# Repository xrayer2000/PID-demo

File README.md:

# PID-DEMO

A dual-axis stepper motor control system based on an STM32F411 microcontroller. The project implements closed-loop position and velocity control using magnetic rotary encoders, PID controllers and configurable motion profiles.

## Mechanical Assembly

The project incorporates three cycloidal reducer designs:

- **Left:** Cycloidal reducers driven by stepper motors, designed by [SweepDynamics](https://github.com/SweepDynamics) and [Promakina](https://github.com/Promakina), respectively.
- **Right:** Cycloidal reducer driven by a BLDC motor, designed by [sirojudinMunir](https://github.com/sirojudinMunir) ([SF-Motion](https://github.com/sirojudinMunir/sf-motion)).

## Features

- **Dual-axis control** – independent control of two stepper motor axes.
- **Closed-loop feedback** – AS5600 magnetic rotary encoders provide position feedback.
- **PID control** – separate position and velocity PID controllers for each axis.
- **Motion profiling** – trapezoidal and triangular position profiles, as well as velocity ramps.
- **Multiple operating modes** – position control, position oscillation, velocity control and velocity oscillation.
- **Configurable parameters** – setpoints, PID gains, oscillation amplitude, period, motor microstepping and step signal duty cycle.
- **OLED interface** – two displays and a rotary encoder with push-button navigation.
- **FreeRTOS** – separate tasks for control, display and main application logic.
- **Serial monitoring** – runtime status and telemetry output for debugging and plotting.

## Hardware

| Component | Description |
|---|---|
| Microcontroller | STM32F411CEU6 (Black Pill) |
| Motor drivers | TMC2209 / step-and-direction driver interface |
| Position sensors | 2 × AS5600 magnetic rotary encoders |
| Motors | Stepper motors |
| Displays | 2 × SH1106 128 × 64 OLED |
| User interface | Rotary encoder and push-button |

The firmware uses separate I²C buses for the two AS5600 sensors and the OLED displays.

### Electronics and Prototyping

## Control Architecture

Each axis has its own state, configuration, position controller, velocity controller, sensor feedback and motion profiles.

The control loop follows this structure:

1. Read the AS5600 encoder.
2. Calculate position, velocity and acceleration.
3. Generate the reference signal according to the selected operating mode.
4. Apply the corresponding PID controller.
5. Convert the controller output into a step frequency and direction.
6. Update the stepper motor driver.

### Operating Modes

| Mode | Description |
|---|---|
| `MODE_posControl` | Move the axis to a specified position using a motion profile. |
| `MODE_posControl_OSC` | Oscillate between positive and negative position targets. |
| `MODE_velControl` | Track a specified velocity using a velocity ramp. |
| `MODE_velControl_OSC` | Oscillate between positive and negative velocity targets. |

### Motion Profiles

The project implements two types of motion profiles:

- **Position profile:** Generates triangular or trapezoidal velocity profiles to move between position targets while respecting velocity and acceleration limits.
- **Velocity profile:** Generates a linear velocity ramp between the initial and target velocity.

### PID Controllers

Each axis has two PID controllers:

- Position PID: regulates position and generates a velocity command.
- Velocity PID: regulates measured velocity against the velocity reference.

The active controller depends on the selected operating mode.

## Software Architecture

The firmware is organized into the following modules:

```text
ArduinoCode/
├── include/
├── lib/
│   ├── AS5600/
│   ├── PID_Controller/
│   ├── PressButton/
│   ├── RotaryEncoderAccel/
│   └── U8g2_Arduino/
├── src/
│   ├── Axis/
│   │   ├── axis.cpp
│   │   └── axis.h
│   ├── TMC2209/
│   │   ├── tmc2209.cpp
│   │   └── tmc2209.h
│   ├── TrapProfile/
│   │   └── TrapProfile.h
│   ├── main.cpp
│   ├── main.h
│   ├── config.h
│   ├── taskMain.cpp
│   ├── taskControl.cpp
│   └── taskDisplay.cpp
├── tools/
│   └── live_plot.py
└── platformio.ini
```

### FreeRTOS Tasks

| Task | Priority | Period | Responsibility |
|---|---:|---:|---|
| Main | 2 | 10 ms | Settings and general application handling |
| Control | 3 | 5 ms | Sensor updates, PID control and motor commands |
| Display | 1 | 10 ms | Menu navigation and OLED updates |

## Development Environment

The firmware is developed using:

- PlatformIO
- Visual Studio Code
- Arduino framework
- STM32 platform (`ststm32`)
- STM32F411CEU board configuration
- STM32FreeRTOS

## Building and Uploading

### 1. Clone the repository

```bash
git clone https://github.com/xrayer2000/PID-demo.git
cd PID-demo
```

### 2. Open the firmware project

Open the `ArduinoCode` directory in Visual Studio Code with the PlatformIO extension installed.

### 3. Build

```bash
pio run
```

### 4. Upload

Connect an ST-LINK programmer to the STM32 board and run:

```bash
pio run -t upload
```

The PlatformIO configuration uses ST-LINK for both uploading and debugging.

## Live Plotting

The project includes `ArduinoCode/tools/live_plot.py` for plotting runtime telemetry from the controller.

The firmware outputs axis status information over the serial connection, which can be used to observe controller behaviour and evaluate tracking performance.

### Position, Velocity and Acceleration

The following plots show the measured position, velocity and acceleration of both axes during position oscillation.

## Project Status

The project is under active development. Hardware configuration, PID tuning and motion-control behaviour may change as the system evolves.

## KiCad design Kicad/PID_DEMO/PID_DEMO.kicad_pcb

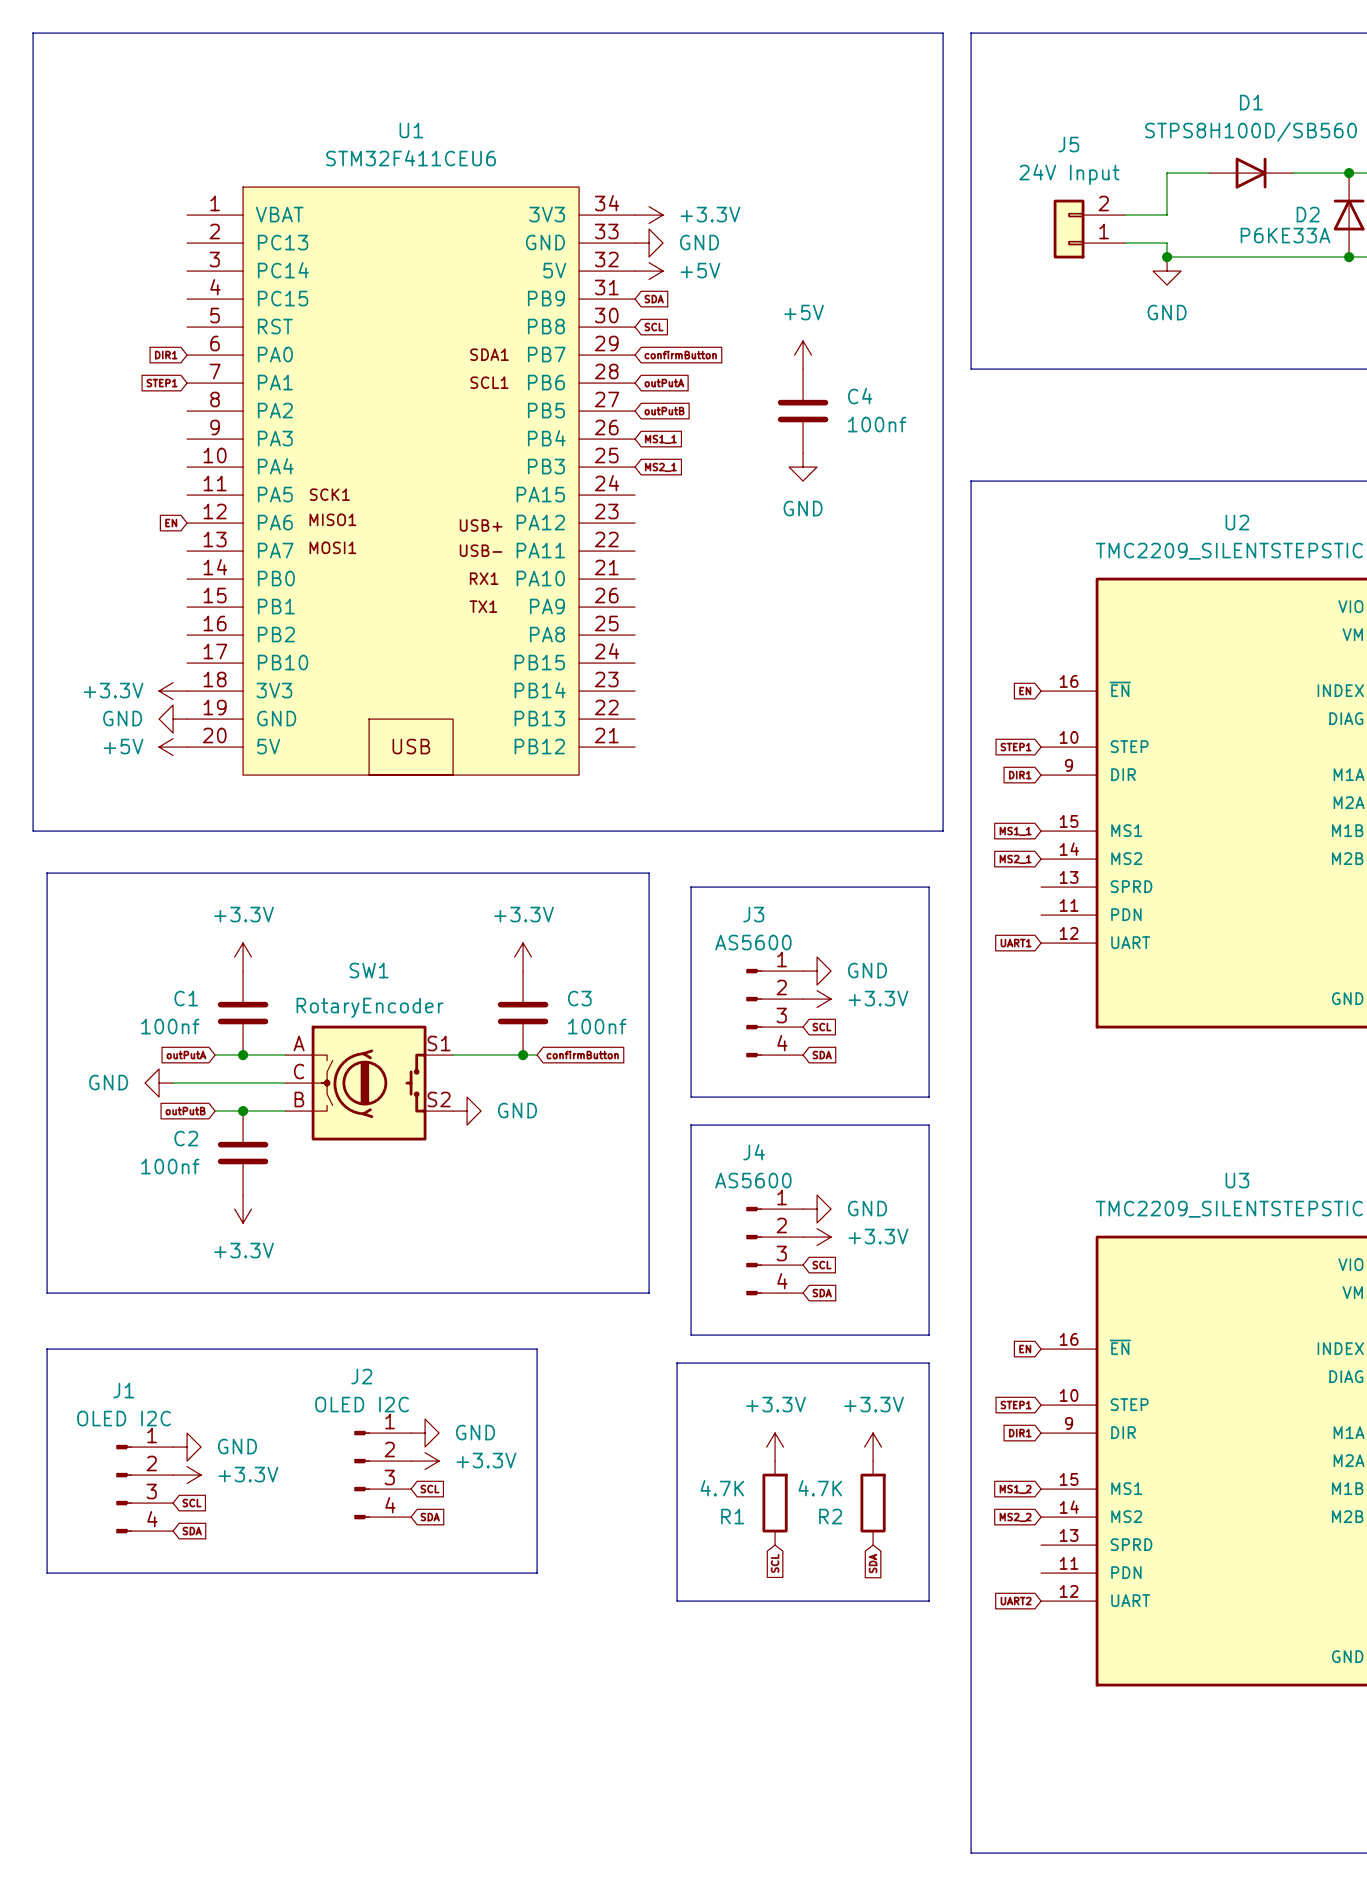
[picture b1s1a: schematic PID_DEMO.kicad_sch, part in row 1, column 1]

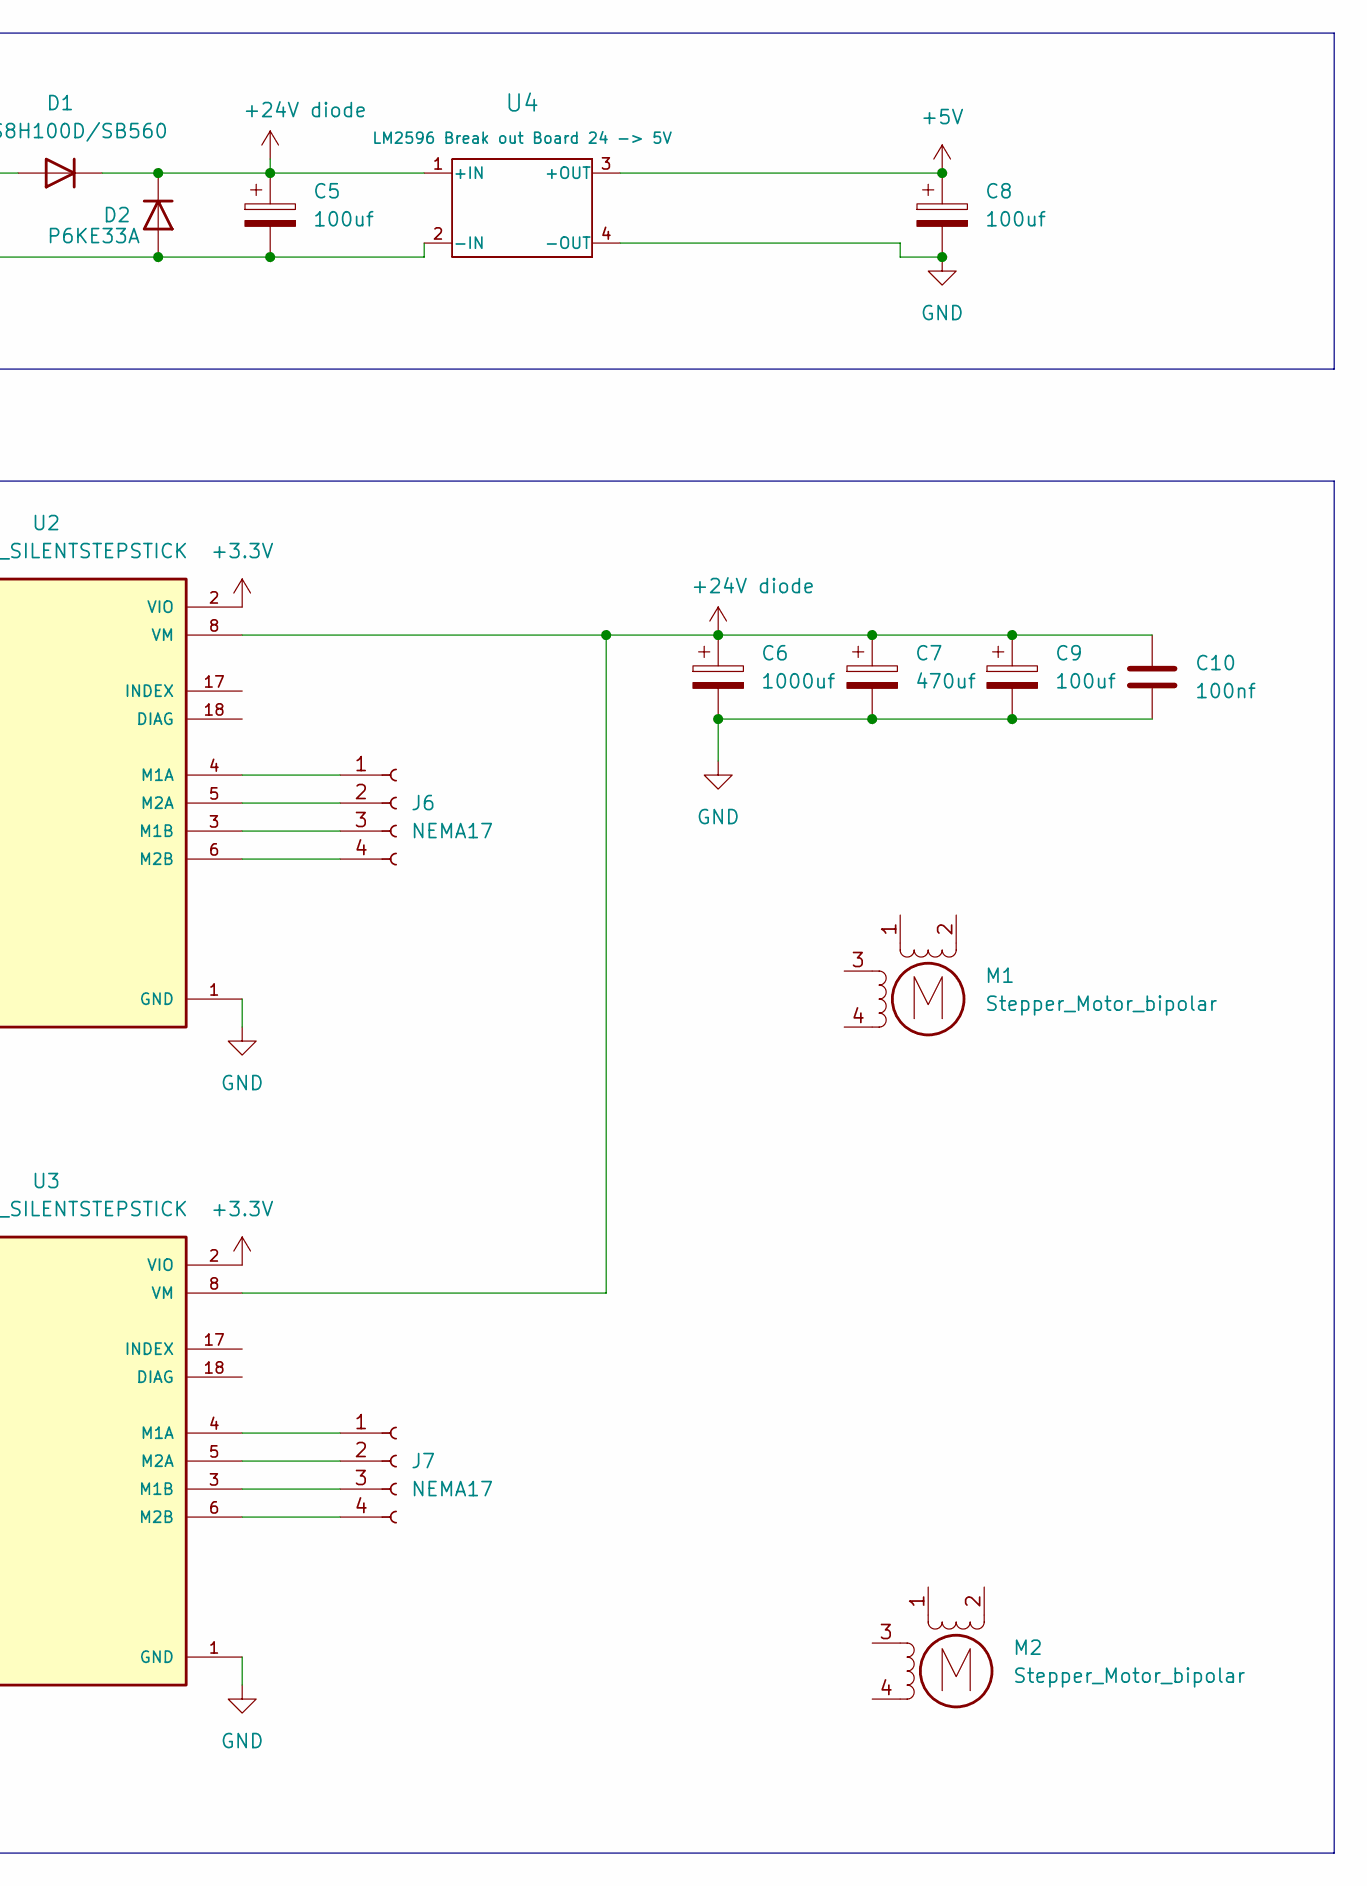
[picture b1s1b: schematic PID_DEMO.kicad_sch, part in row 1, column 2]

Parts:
C1, C2, C3, C4, C10: 100nf; C_Disc_D3.0mm_W1.6mm_P2.50mm
C5, C8: 100uf; CP_Radial_D5.0mm_P2.00mm
C6: 1000uf; CP_Radial_D16.0mm_P7.50mm
C7: 470uf; CP_Radial_D13.0mm_P5.00mm
C9: 100uf; CP_Radial_D10.0mm_P5.00mm
D1: STPS8H100D/SB560; D_DO-15_P5.08mm_Vertical_AnodeUp
D2: P6KE33A; D_DO-15_P5.08mm_Vertical_AnodeUp
J1, J2: OLED I2C; ssd1306_1.3''
J3, J4: AS5600; JST_XH_B4B-XH-A_1x04_P2.50mm_Vertical
J5: 24V Input; TerminalBlock_Phoenix_MKDS-1,5-2_1x02_P5.00mm_Horizontal
J6, J7: NEMA17; JST_XH_B4B-XH-A_1x04_P2.50mm_Vertical
M1, M2: Stepper_Motor_bipolar; NEMA17
R1, R2: 4.7K; R_Axial_DIN0207_L6.3mm_D2.5mm_P7.62mm_Horizontal
SW1: RotaryEncoder; RotaryEncoder_Alps_EC11E-Switch_Vertical_H20mm
U1: STM32F411CEU6; YAAJ_BlackPill_1
U2, U3: TMC2209_SILENTSTEPSTICK; MODULE_TMC2209_SILENTSTEPSTICK; PARTREV 1.20
U4: LM2596 Break out Board 24 -> 5V; DC_DC_LM2596_small

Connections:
+3.3V: C1.1, C2.2, C3.1, J1.2, J2.2, J3.2, J4.2, R1.2, R2.2, U1.18 (3V3), U1.34 (3V3), U2.2 (VIO), U3.2 (VIO)
+5V: C4.1, C8.1, U1.20 (5V), U1.32 (5V), U4.3 (+OUT)
+24V diode: C5.1, C6.1, C7.1, C9.1, C10.1, D1.1 (K), D2.1 (K), U2.8 (VM), U3.8 (VM), U4.1 (+IN)
DIR1: U1.6 (PA0), U2.9 (DIR), U3.9 (DIR)
EN: U1.12 (PA6), U2.16 (~EN), U3.16 (~EN)
GND: C4.2, C5.2, C6.2, C7.2, C8.2, C9.2, C10.2, D2.2 (A), J1.1, J2.1, J3.1, J4.1, J5.1, SW1.C, SW1.S2, U1.19 (GND), U1.33 (GND), U2.1 (GND), U2.7 (GND), U3.1 (GND), U3.7 (GND), U4.2 (-IN), U4.4 (-OUT)
MS1_1: U1.26 (PB4), U2.15 (MS1)
MS1_2: U3.15 (MS1)
MS2_1: U1.25 (PB3), U2.14 (MS2)
MS2_2: U3.14 (MS2)
unnamed: D1.2 (A), J5.2
unnamed: J6.1, U2.4 (M1A)
unnamed: J6.2, U2.5 (M2A)
unnamed: J6.3, U2.3 (M1B)
unnamed: J6.4, U2.6 (M2B)
unnamed: J7.1, U3.4 (M1A)
unnamed: J7.2, U3.5 (M2A)
unnamed: J7.3, U3.3 (M1B)
unnamed: J7.4, U3.6 (M2B)
SCL: J1.3, J2.3, J3.3, J4.3, R1.1, U1.30 (PB8)
SDA: J1.4, J2.4, J3.4, J4.4, R2.1, U1.31 (PB9)
STEP1: U1.7 (PA1), U2.10 (STEP), U3.10 (STEP)
UART1: U2.12 (UART)
UART2: U3.12 (UART)
confirmButton: C3.2, SW1.S1, U1.29 (PB7)
outPutA: C1.2, SW1.A, U1.28 (PB6)
outPutB: C2.1, SW1.B, U1.27 (PB5)

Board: 2 copper layers, 28 parts (5 on the bottom side), 23 nets, no tracks yet.

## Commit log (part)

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2024-11-24 added PID_DEMO.ino
2024-11-24 Update README.md
    Ki
2024-11-29 updated PID demo 2024-11-29
2024-11-30 added PID_DEMO_Angle
2024-11-30 modified PID-demo_Angle 2024-11-30
2026-03-22 added main.inom new start for Stepper motors
2026-03-23 fixed hardware timmer stepTimer->refresh(); // force immediate reload
2026-06-11 added FreeRTOS, TaskDisplay.h .cpp
2026-06-12 added structure, added a bunch of new files for structure
